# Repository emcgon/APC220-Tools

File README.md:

# APC220-Tools
A collection of tools for using and configuring DFRobot APC220 radio modules

## apc220monitor.py
Listens on the specified serial port (presumably with an APC220 radio connected to it) and outputs any data received to the console, also optionally logging it to a file.

What makes this more useful than just using PuTTY or similar is that this script forces the RTS pin high. In the USB-to-APC220 adapter than is ususally used to connect the APC220 radio to a PC, RTS is wired to the EN pin. Forcing RTS high thus enables the radio (which is necessary for it to send or receive anything) without having to resort to hacking on jumper wires.

### Instructions for use
```
$ python3 apc220monitor.py  -h
usage: apc220monitor.py [-h] comPort {2400,4800,9600,19200,38400} outFile

Monitor data from a serial port (an APC220 radio connected via a USB adapter). Displays the output to the console and optionally writes it to a file.

positional arguments:
  comPort               "COMx" should be the COM port that the APC220 radio is connected to (typically COM2, but check this in Device Manager to be sure)
  {2400,4800,9600,19200,38400}
                        "SPEED" is the baud rate. It is typically 9600 unless you have set your APC220 radio to something different.
  outFile               "output-file" is the name of the file to save output to. You can specify a value of "nul" here if you don't want data saved to a file.

options:
  -h, --help            show this help message and exit
```

#### Windows:
```
C:\APC220-Tools>python3 apc220monitor.py com11 9600 a.out
Logging received data to a.out
Hello from an APC220 connected to a Linux machine!
Bye!

C:\APC220-Tools>type a.out
================================================================================
Logging started at 2024-02-21 22:16:38.862246
================================================================================
Hello from an APC220 connected to a Linux machine!
```

#### Linux:
```
$ sudo python3 apc220monitor.py  /dev/ttyUSB0 9600 a.out
Logging received data to a.out
hello, world!
^CBye!
$ cat a.out 
================================================================================
Logging started at 2024-02-21 22:14:43.543053
================================================================================
hello, world!
$
```

## apc220send.py 
Reads input from standard input and transmits it via the specified serial port.

Again, this script forces RTS high, enabling the radio without having to hard-wire the EN pin.

### Instructions for use
```
$ python3 apc220send.py  -h
usage: apc220send.py [-h] [-v] comPort {2400,4800,9600,19200,38400}

Read data from standard input and transmit it via an APC220 radio connected to the specified serial port.

positional arguments:
  comPort               "COMx" should be the COM port that the APC220 radio is connected to (typically COM2, but check this in Device Manager to be sure)
  {2400,4800,9600,19200,38400}
                        "SPEED" is the baud rate. It is typically 9600 unless you have set your APC220 radio to something different.

optional arguments:
  -h, --help            show this help message and exit
  -v, --verbose         Produce verbose output
```

#### Linux:
```
$ sudo python3 apc220send.py /dev/ttyUSB0 9600
Reading from standard input: end with CTRL-D on a line on its own
hello, world!
14
```
If you are typing the data to be sent (rather than piping it in from a file or another program), press CTRL-D to terminate.  The number that is displayed is the number of bytes read and transmitted.

#### Windows:
```
C:\APC220-Tools>python3 apc220send.py com11 9600
Reading from standard input: end with CTRL-Z on a line on its own
hello, world!
^Z
14
```
If you are typing the data to be sent (rather than piping it in from a file or another program), press CTRL-Z to terminate.  The number that is displayed is the number of bytes read and transmitted.

Alternatively...
```
C:\APC220-Tools>echo Mary had a little lamb | python3 apc220send.py com11 9600
24
```
...does exactly what you would expect. At the receiving end...
```
$ sudo python3 apc220monitor.py  /dev/ttyUSB0 9600 a.out
Logging received data to a.out
Mary had a little lamb 
^CBye!

$ cat a.out 
================================================================================
Logging started at 2024-02-21 22:26:13.318536
================================================================================
Mary had a little lamb 
```
Interactive-mode (-i, --interactive) reads continuously from standard input and transmits one line at a time. This may be more

## rfmagic
The OG tool for reprogramming APC220 radios is called RF Magic and it is (IMHO) nasty. It is only available on Windows and - in my experience - is very hit-and-miss. This is a reimplementation of RF Magic as a Python command-line tool along with an analysis of the protocol.

## APC220Programmer
Schematic and source-code for a standalone hardware programmer based on an Arduino Nano and a 16x2 LCD screen allowing APC220 radios to be quickly reprogrammed without the need for a laptop or a USB adapter.

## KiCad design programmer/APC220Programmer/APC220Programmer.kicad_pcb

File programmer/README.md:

# APC220 Programmer
An Arduino program and schematic for a hardware programmer for APC220 radios. See a quick demo (of an older prototype) at https://www.youtube.com/watch?v=wyKSJeXSkzc (the video was intended for a few people involved in organising the local [CanSat](https://esero.ie/cansat/) competition: that's what the references to "launchers" are all about).

Here are 3D renders of the front and back of the current iteration of the PCB from KiCad:-

## Schematic

## Bill of Materials

|Part|Description|Notes|
|----|-----------|-----|
|A2|Arduino Nano v3.x|	
|BT1|Molex KK254 (P/N 22232021) power connector or  similar _or_ 2x1 2.54mm pin Header|For connection to an off-board 9V PP3 battery clip|
|D1|1N4001|For reverse-polarity protection: almost any diode would do. If you trust yourself not to connect the battery the wrong way around, you could omit this and just fit a wire jumper 😉|
|DS1|16x2 LCD Display with "standard" Hitachi HD44780 16-pin interface||
|Q1|2N7000 MOSFET|TO92 case|
|R1|10K resistor|6.5mm, 1/4W axial|
|R2,R3|1K resistor|6.5mm, 1/4W axial|
|R4|220R resistor|6.5mm, 1/4W axial. Only required if your display doesn't have an on-board current-limiting resistor for the backlight (some do, some don't). Can be replaced with a wire link otherwise.|
|RV1|10K trimpot|Bourns 3296W vertical|
|SW1|2x1 2.54mm pin Header (off-board SPST power switch)|
|SW2|Rotary Encoder with Switch|ALPS EC11E series or equivalent|
|U1|Adafruit BMP390 Module (https://www.adafruit.com/product/4816)|Optional...see note below|
|U2|MPXH6115A6U/T1|Optional...see note below|
|U3|Socket for APC220: 7x1 and 2x1 pin-header sockets|
|PCB||
|Case|PCB dimensioned to fit in a Hammond Manufacturing 1591CS box|
|9V PP3 Batter Clip|Connects to BT1 connector listed above|
|Panel-mounted SPST power switch|Connects to SW1 listed above|

U1 and U2 are barometric pressure sensors and are both optional. If you don't want a barometer function, you can omit both. If you _do_ want the barometer function, you only need one or the other. U1 (the Adafruit one) is probably preferable: it is cheaper, easier to obtain and more accurate (and we love Adafruit because they are wonderful people :heart:!)

## Assembly Tips
- It is a tight fit into a Hammond Manufacturing 1591CS box, but it does fit. In my prototype build, I had to secure the battery to the lid with a Velco cable-tie to fit it in. 
- The PCB is attached to the case by M3 bolts which go through the display and the PCB and the rotary encoder. Use spacers between the display and PCB mounting holes to keep the display parallel to the PCB. Make those spacers large enough so that the front surface of the display PCB is in the same plane as the top surface of the rotary encoder. This should ensure that the entire assembly is securly attached to the case and should leave room under the display so that it doesn't come into contact with the Arduino pins
- Mount the Arduino Nano high enough off the surface of the PCB so that there is only a minimial amount of pin length protruding below. Again, the objective is to ensure that Arduino pins sticking out underneath the display don't touch any part of the display
- When mounting the sockets for the APC220, temporary put an APC220 into the two sockets to ensure perfect alignment
- Mount the display last.  It won't be possible to solder the Arduino in if you have mounted the display first.

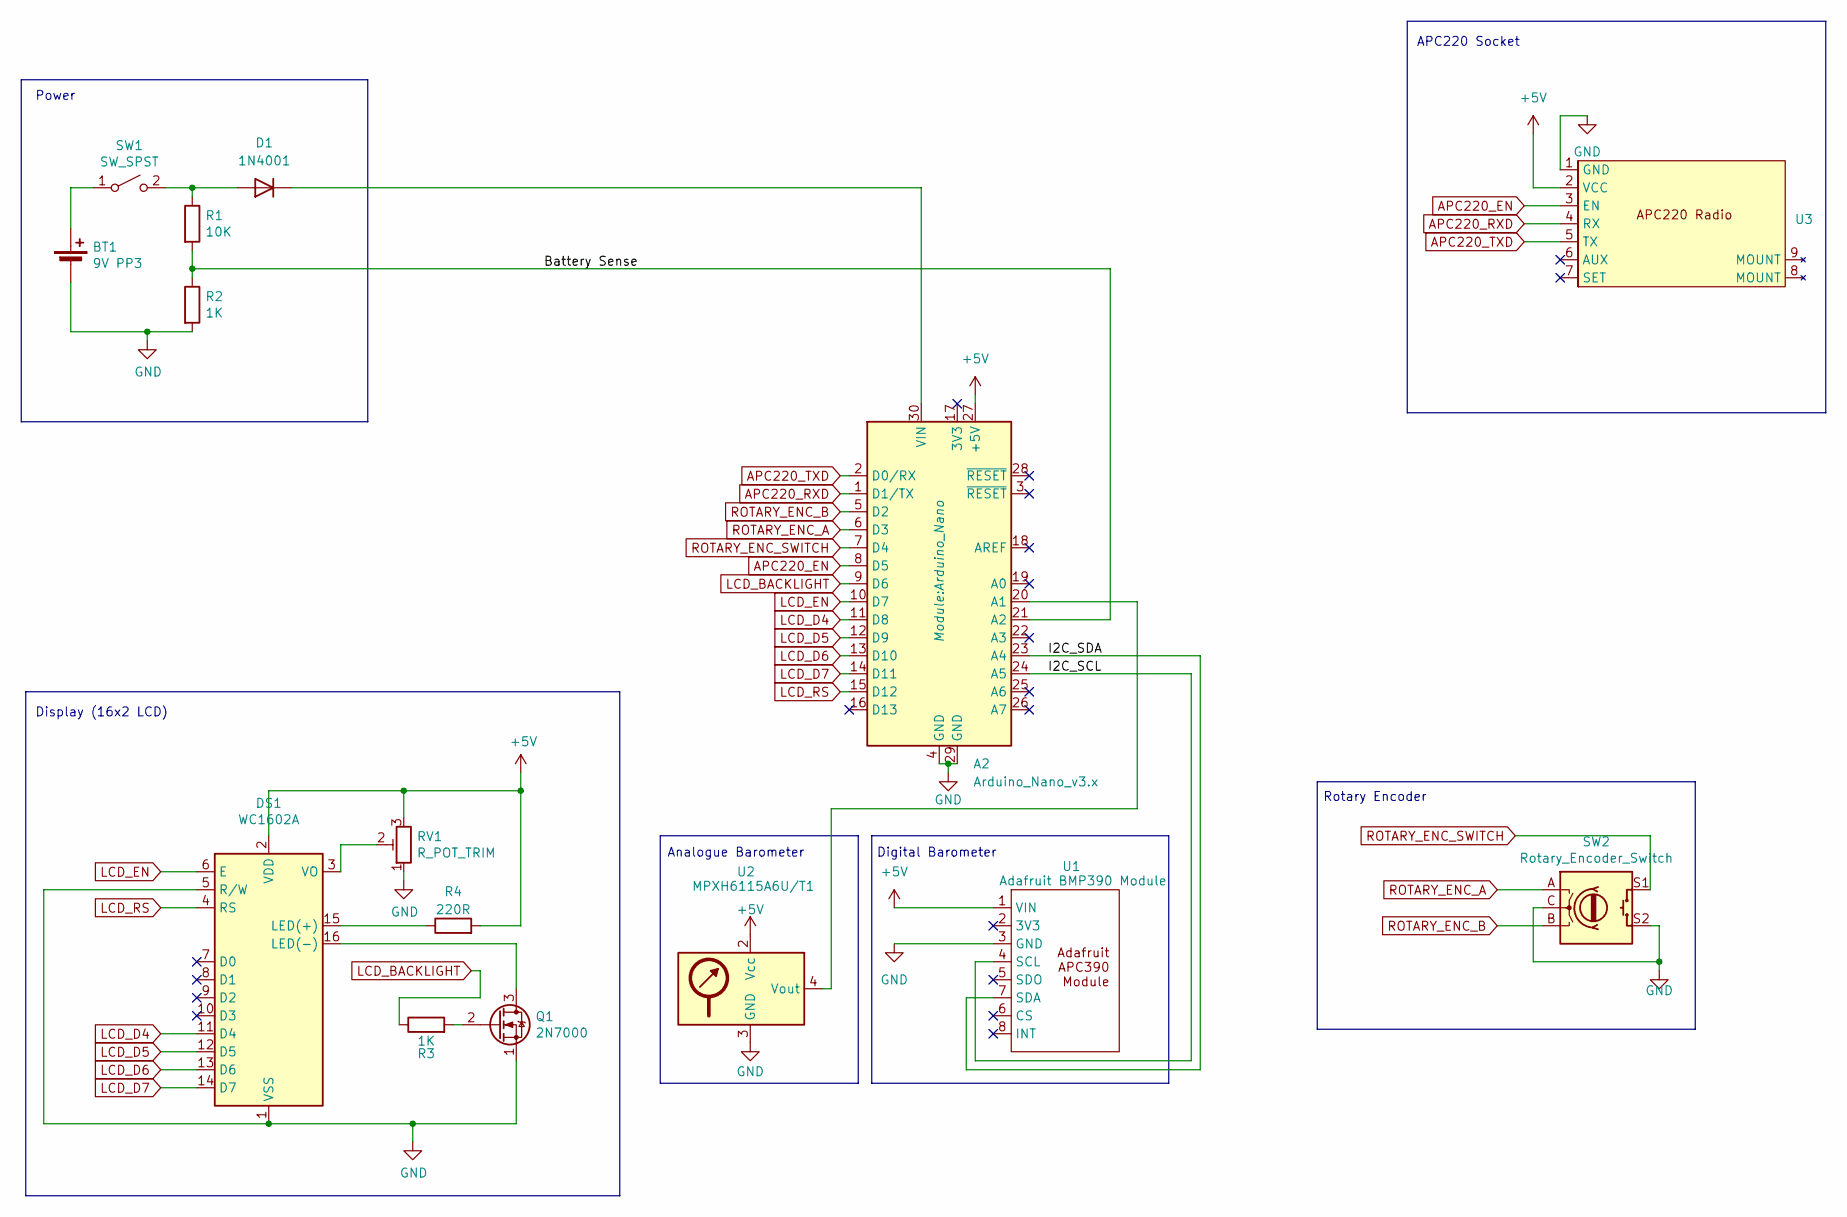
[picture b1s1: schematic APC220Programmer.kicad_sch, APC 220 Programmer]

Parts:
A2: Arduino_Nano_v3.x; Arduino_Nano
BT1: 9V PP3; Molex_KK-254_AE-6410-02A_1x02_P2.54mm_Vertical
D1: 1N4001; D_A-405_P10.16mm_Horizontal
DS1: WC1602A
Q1: 2N7000; TO-92_Inline
R1: 10K; R_Axial_DIN0207_L6.3mm_D2.5mm_P10.16mm_Horizontal
R2, R3: 1K; R_Axial_DIN0207_L6.3mm_D2.5mm_P10.16mm_Horizontal
R4: 220R; R_Axial_DIN0207_L6.3mm_D2.5mm_P10.16mm_Horizontal
RV1: R_POT_TRIM; Potentiometer_Bourns_3296W_Vertical
SW1: SW_SPST; PinHeader_1x02_P2.54mm_Vertical
SW2: Rotary_Encoder_Switch; RotaryEncoder_Alps_EC11E-Switch_Vertical_H20mm
U1: Adafruit BMP390 Module
U2: MPXH6115A6U/T1; Freescale_98ARH99089A
U3: APC220 Radio

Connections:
+5V: A2.27 (+5V), DS1.2 (VDD), R4.2, RV1.3, U1.1 (VIN), U2.2 (Vcc), U3.2 (VCC)
/Battery Sense: A2.21 (A2), R1.2, R2.1
/I2C_SCL: A2.24 (A5), U1.4 (SCL)
/I2C_SDA: A2.23 (A4), U1.7 (SDA)
APC220_EN: A2.8 (D5), U3.3 (EN)
APC220_RXD: A2.1 (D1/TX), U3.4 (RX)
APC220_TXD: A2.2 (D0/RX), U3.5 (TX)
GND: A2.4 (GND), A2.29 (GND), BT1.2 (-), DS1.1 (VSS), DS1.5 (R/W), Q1.1 (S), R2.2, RV1.1, SW2.C, SW2.S2, U1.3 (GND), U2.3 (GND), U3.1 (GND)
LCD_BACKLIGHT: A2.9 (D6), R3.1
LCD_D4: A2.11 (D8), DS1.11 (D4)
LCD_D5: A2.12 (D9), DS1.12 (D5)
LCD_D6: A2.13 (D10), DS1.13 (D6)
LCD_D7: A2.14 (D11), DS1.14 (D7)
LCD_EN: A2.10 (D7), DS1.6 (E)
LCD_RS: A2.15 (D12), DS1.4 (RS)
unnamed: A2.20 (A1), U2.4 (Vout)
unnamed: A2.30 (VIN), D1.1 (K)
unnamed: BT1.1 (+), SW1.1 (A)
unnamed: D1.2 (A), R1.1, SW1.2 (B)
unnamed: DS1.15 (LED(+)), R4.1
unnamed: DS1.16 (LED(-)), Q1.3 (D)
unnamed: DS1.3 (VO), RV1.2
unnamed: Q1.2 (G), R3.2
ROTARY_ENC_A: A2.6 (D3), SW2.A
ROTARY_ENC_B: A2.5 (D2), SW2.B
ROTARY_ENC_SWITCH: A2.7 (D4), SW2.S1

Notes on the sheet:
Analogue Barometer
APC220 Socket
Digital Barometer
Power
Display (16x2 LCD)
Rotary Encoder

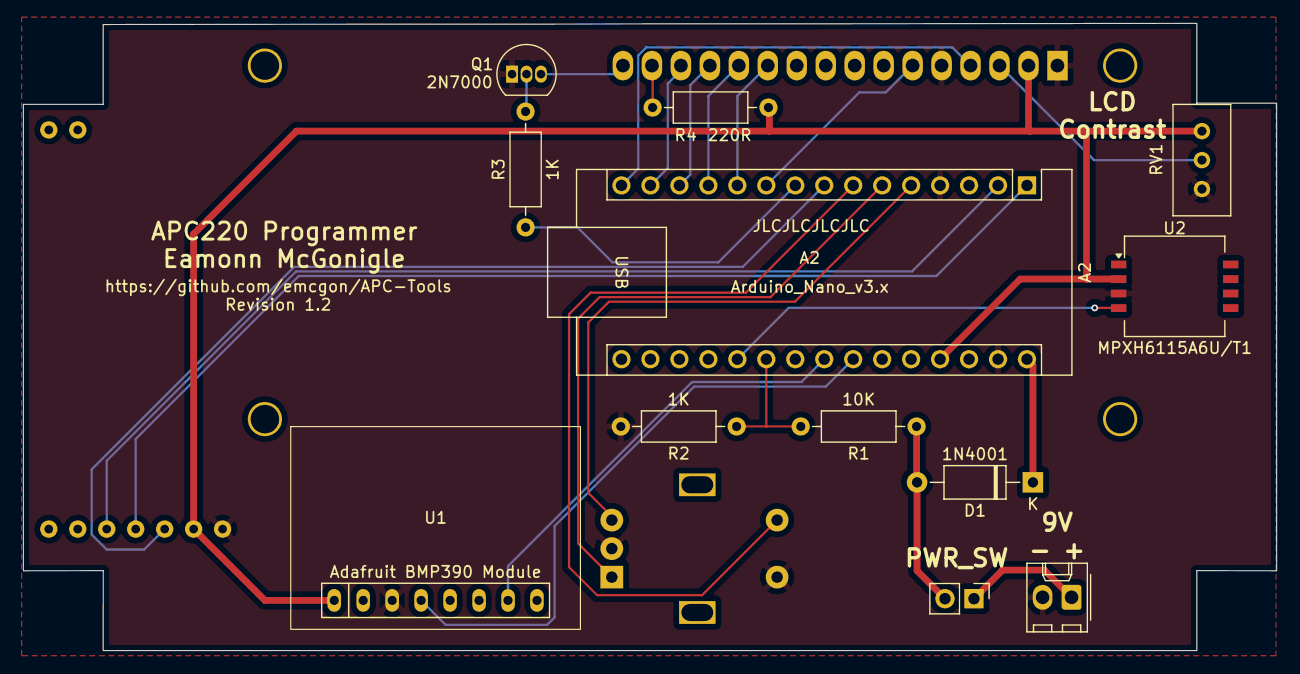
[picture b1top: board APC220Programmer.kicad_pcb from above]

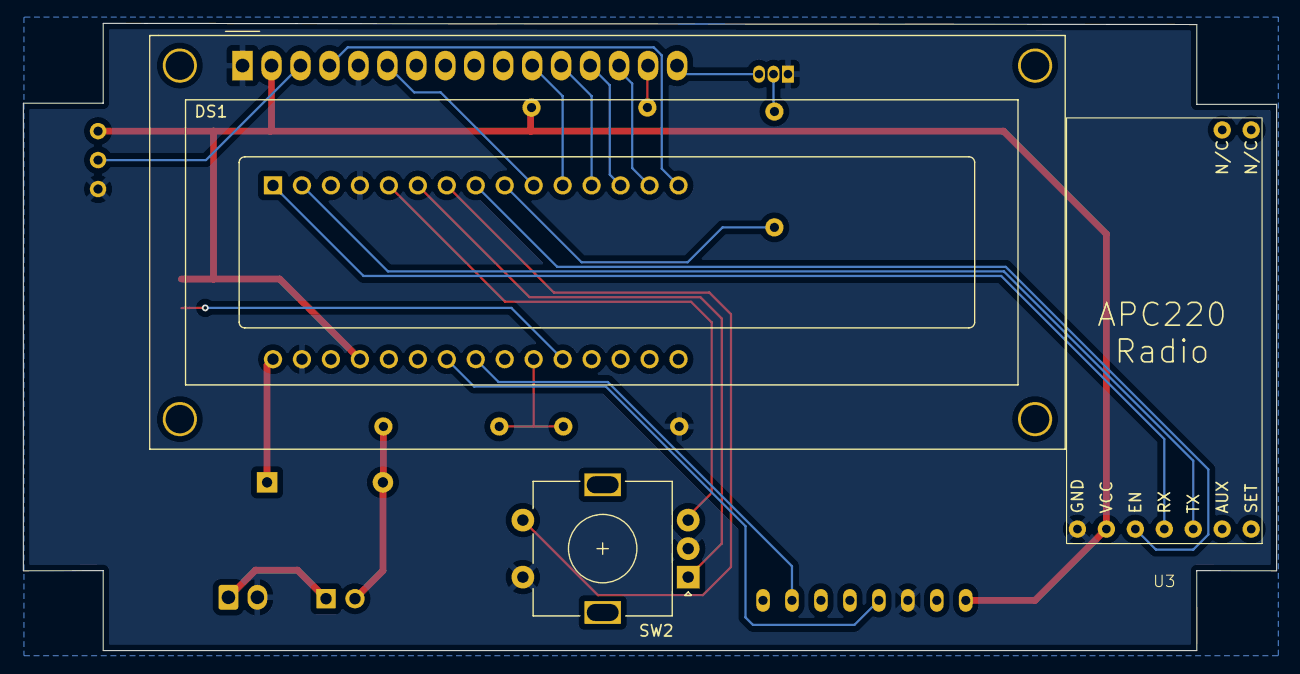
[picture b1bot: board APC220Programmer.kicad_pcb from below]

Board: 2 copper layers, 109.9 x 55.0 mm, 15 parts (3 on the bottom side), 26 nets.

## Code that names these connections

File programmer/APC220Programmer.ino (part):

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// #define DEBUG

// Pin assignments for APC220
#define APC220_EN_PIN     5
// Pin assignments for LCD
#define LCD_BACKLIGHT_PIN 6    // PWM-capable on an Atmega 328 !!
#define LCD_ENABLE_PIN    7
#define LCD_D4_PIN        8
#define LCD_D5_PIN        9
#define LCD_D6_PIN        10
#define LCD_D7_PIN        11
#define LCD_RS_PIN        12

// Pin assignements for rotary encoder
#define ROTARY_A_PIN       2    // Interrupt 0
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/*
** Global variables
*/
LiquidCrystal lcd(LCD_RS_PIN, LCD_ENABLE_PIN, LCD_D4_PIN, LCD_D5_PIN, LCD_D6_PIN, LCD_D7_PIN);
Encoder rotary(ROTARY_B_PIN, ROTARY_A_PIN);
int currentSerialBaudRate=-1;
unsigned long backlightOffTime=0;
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void setup() 
{
    // Initialise LCD
    pinMode(LCD_BACKLIGHT_PIN,OUTPUT);
    BacklightOn();
    lcd.begin(16, 2);
    lcd.setCursor(0,0); lcd.print("==APC220 Magic==");
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    digitalWrite(ROTARY_BUTTON_PIN, HIGH);
        
    // Set up serial interface to APC220 radio
    pinMode(APC220_EN_PIN,OUTPUT);
    digitalWrite(APC220_EN_PIN,LOW);

    byte smiley[] = {
        B00000,
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        lcd.print("Not found \002");
    }
    Serial.end();
    digitalWrite(APC220_EN_PIN,LOW);
    WaitForClick();
}

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        WaitForClick();
    }
    Serial.end();
    digitalWrite(APC220_EN_PIN,LOW);
}


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    }
    else
    {
        digitalWrite(APC220_EN_PIN, HIGH);
        delay(100);
        Serial.begin(baudRateTable[currentSerialBaudRate]);
        Serial.println("Humpty Dumpty sat on a wall, Humpty Dumpty had a great fall");
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    }
    lcd.print("Monitoring...");
    lcd.setCursor(0,1);
    digitalWrite(APC220_EN_PIN, HIGH);
    delay(100);
    Serial.begin(baudRateTable[currentSerialBaudRate]);
    while (!DebounceRotaryButton())
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            if (apc220_en_state)
            {
                // Is HIGH - go low for 156ms
                digitalWrite(APC220_EN_PIN, apc220_en_state = LOW);
                next_en_change = millis() + 156;        // TODO: Tune this with oscilloscope
            }
            else
            {
                // Is LOW - go HIGH for 326ms
                digitalWrite(APC220_EN_PIN, apc220_en_state = HIGH);
                next_en_change = millis() + 326;
            }
        }
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        }
        if (got_consecutive_a7 >= 3)
        {
            digitalWrite(APC220_EN_PIN, HIGH);
            return(1);
        }
        if (millis() >= give_up_at)
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{
    if ((backlightOffTime > 0) && (millis() > backlightOffTime))
    {
        digitalWrite(LCD_BACKLIGHT_PIN,LOW);
        backlightOffTime = 0;
    }
}
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{
    if (backlightOffTime == 0)
    {
        digitalWrite(LCD_BACKLIGHT_PIN,HIGH);
    }
    backlightOffTime = millis() + BACKLIGHT_TIMEOUT;
}
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
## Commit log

2024-02-20 Create deleteme
2024-02-20 Create rfmagic
2024-02-20 Fixed error in Write()
    Was using radiobaud for both the radio and the serial baud rate
2024-02-21 Fixed typos
2024-02-21 Fixes to rfmagic.py
2024-02-21 Update apc220monitor.py
    Added option for "-" to prevent logging to a file
2024-02-21 Update README.md
    Empty change for git practice
2024-02-26 Added interactive-mode to apc220send.py
2024-02-26 Removed explicit "interactive-mode" and made it the default when reading from standard input
2024-02-27 Rework Ping() to send continuously and to include a reading of atmospheric pressure (assuming an MPX4115 or MPXA6115A on A2)
2024-03-08 Updated schematic
    Updated schematic to the version with the Arduino Nano and support for the MPX4115A/MPXA6115 barometric pressure sensor. I have ordered PCBs based on this version and am waiting on those to validate 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
2024-03-08 Update APC220Programmer.ino
    Fixed bug where wrong ADC voltage reference used for barometer
2024-03-13 Added KiCad files
2024-03-13 Updated schematic
2024-03-13 Removed cache file and added to .gitignore
2024-03-13 Updated ZIP file containing Gerber and drill files
2024-03-13 Added fp-info-cache
2024-03-13 Begin adding conditional compilation support for two barometer options
2024-03-13 Factor out GetPressure()
2024-03-13 Small fixes
2024-03-14 Grafted in code for BMP390
2024-03-15 Reworked main menu
2024-03-15 Lots of fixes testing with hardware (but not final hardware)
2024-03-15 Further tweaks
2024-03-15 Started on BoM
2024-03-15 Improve BoM
2024-03-17 Minor improvements
2024-03-17 Minor board revisions
2024-03-19 Added some assembly tips
2024-03-28 Added current-limiting resistor to display backlight supply
2024-03-28 Added current-limiting resistor for display backlight. Replaced rounded corners with square corners
2024-03-28 Updated 3D renders
2024-03-28 Bumped revision number
2024-03-28 Added to Assembly Tips
2024-03-28 Updated schematic plot
2024-03-28 Fixed typo
